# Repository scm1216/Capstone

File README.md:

# Capstone Project Aura

## Main Project
AURA -  Air & UV Real-time Alerts
Compact and smart device designed to monitor enverinmental conditions in real-time and alerts users to potentially harmful exposureswhile hiking, backpacking or engaging in other outdoor activities.
* UV radiations levels.
* Air Queality
* Pollen presence
* Ambient temperature

### Project Components Include:
1. Particle photon 2
2. MP3 player
3. Laser PM2.5 Sensor (HM3301)
4. UV sensor
5. BME 280
6. Rechargable battery

### 3D designs

####  Created by Sofia Cortes, 07 - APR - 2025
Check out this project and others on my https://www.hackster.io/sofiacortes

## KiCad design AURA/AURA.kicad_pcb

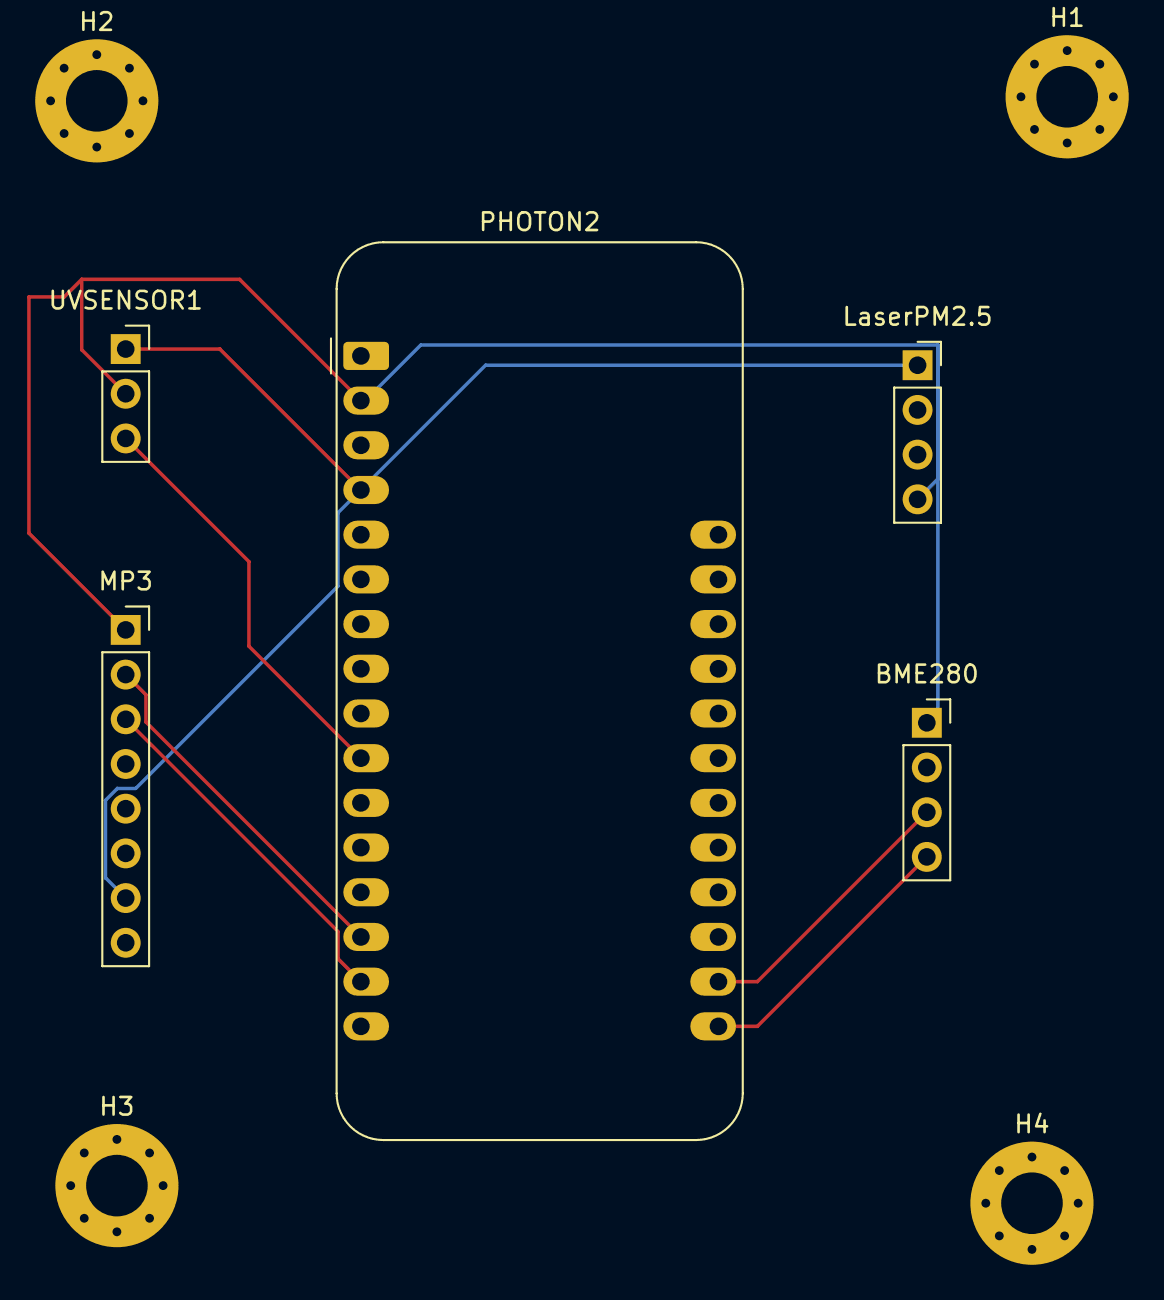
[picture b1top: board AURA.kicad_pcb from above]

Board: 2 copper layers, 9 parts (0 on the bottom side), 7 nets.

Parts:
BME280: Conn_01x04; PinSocket_1x04_P2.54mm_Vertical
H1, H2, H3, H4: MountingHole; MountingHole_3.5mm_Pad_Via
LaserPM2.5: Conn_01x04; PinSocket_1x04_P2.54mm_Vertical
MP3: Conn_01x08; PinSocket_1x08_P2.54mm_Vertical
PHOTON2: Adafruit_Feather_Generic; Adafruit_Feather
UVSENSOR1: Conn_01x03; PinSocket_1x03_P2.54mm_Vertical

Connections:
unnamed: BME280.1, LaserPM2.5.4, MP3.1, PHOTON2.2 (3V3), UVSENSOR1.2
unnamed: BME280.2, LaserPM2.5.1, MP3.7, PHOTON2.4 (GND), UVSENSOR1.1
unnamed: BME280.3, LaserPM2.5.2, PHOTON2.18 (SCL)
unnamed: BME280.4, LaserPM2.5.3, PHOTON2.17 (SDA)
unnamed: MP3.2, PHOTON2.14 (RX)
unnamed: MP3.3, PHOTON2.15 (TX)
unnamed: PHOTON2.10 (A5), UVSENSOR1.3

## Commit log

2025-04-07 Capstone
2025-04-13 Working code
